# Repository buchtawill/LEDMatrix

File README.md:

# LEDMatrix
12x32 SMD LED matrix using ATmega328

### LED matrix 0805
This folder contains the schematic board files for the physical device.

### Image Stuff
Contains the java program that takes a jpg and generates an array that can be read by the ATmega.

### led-matrix
Contains the C++ code that runs on the ATmega. The Arduino development environment was used.

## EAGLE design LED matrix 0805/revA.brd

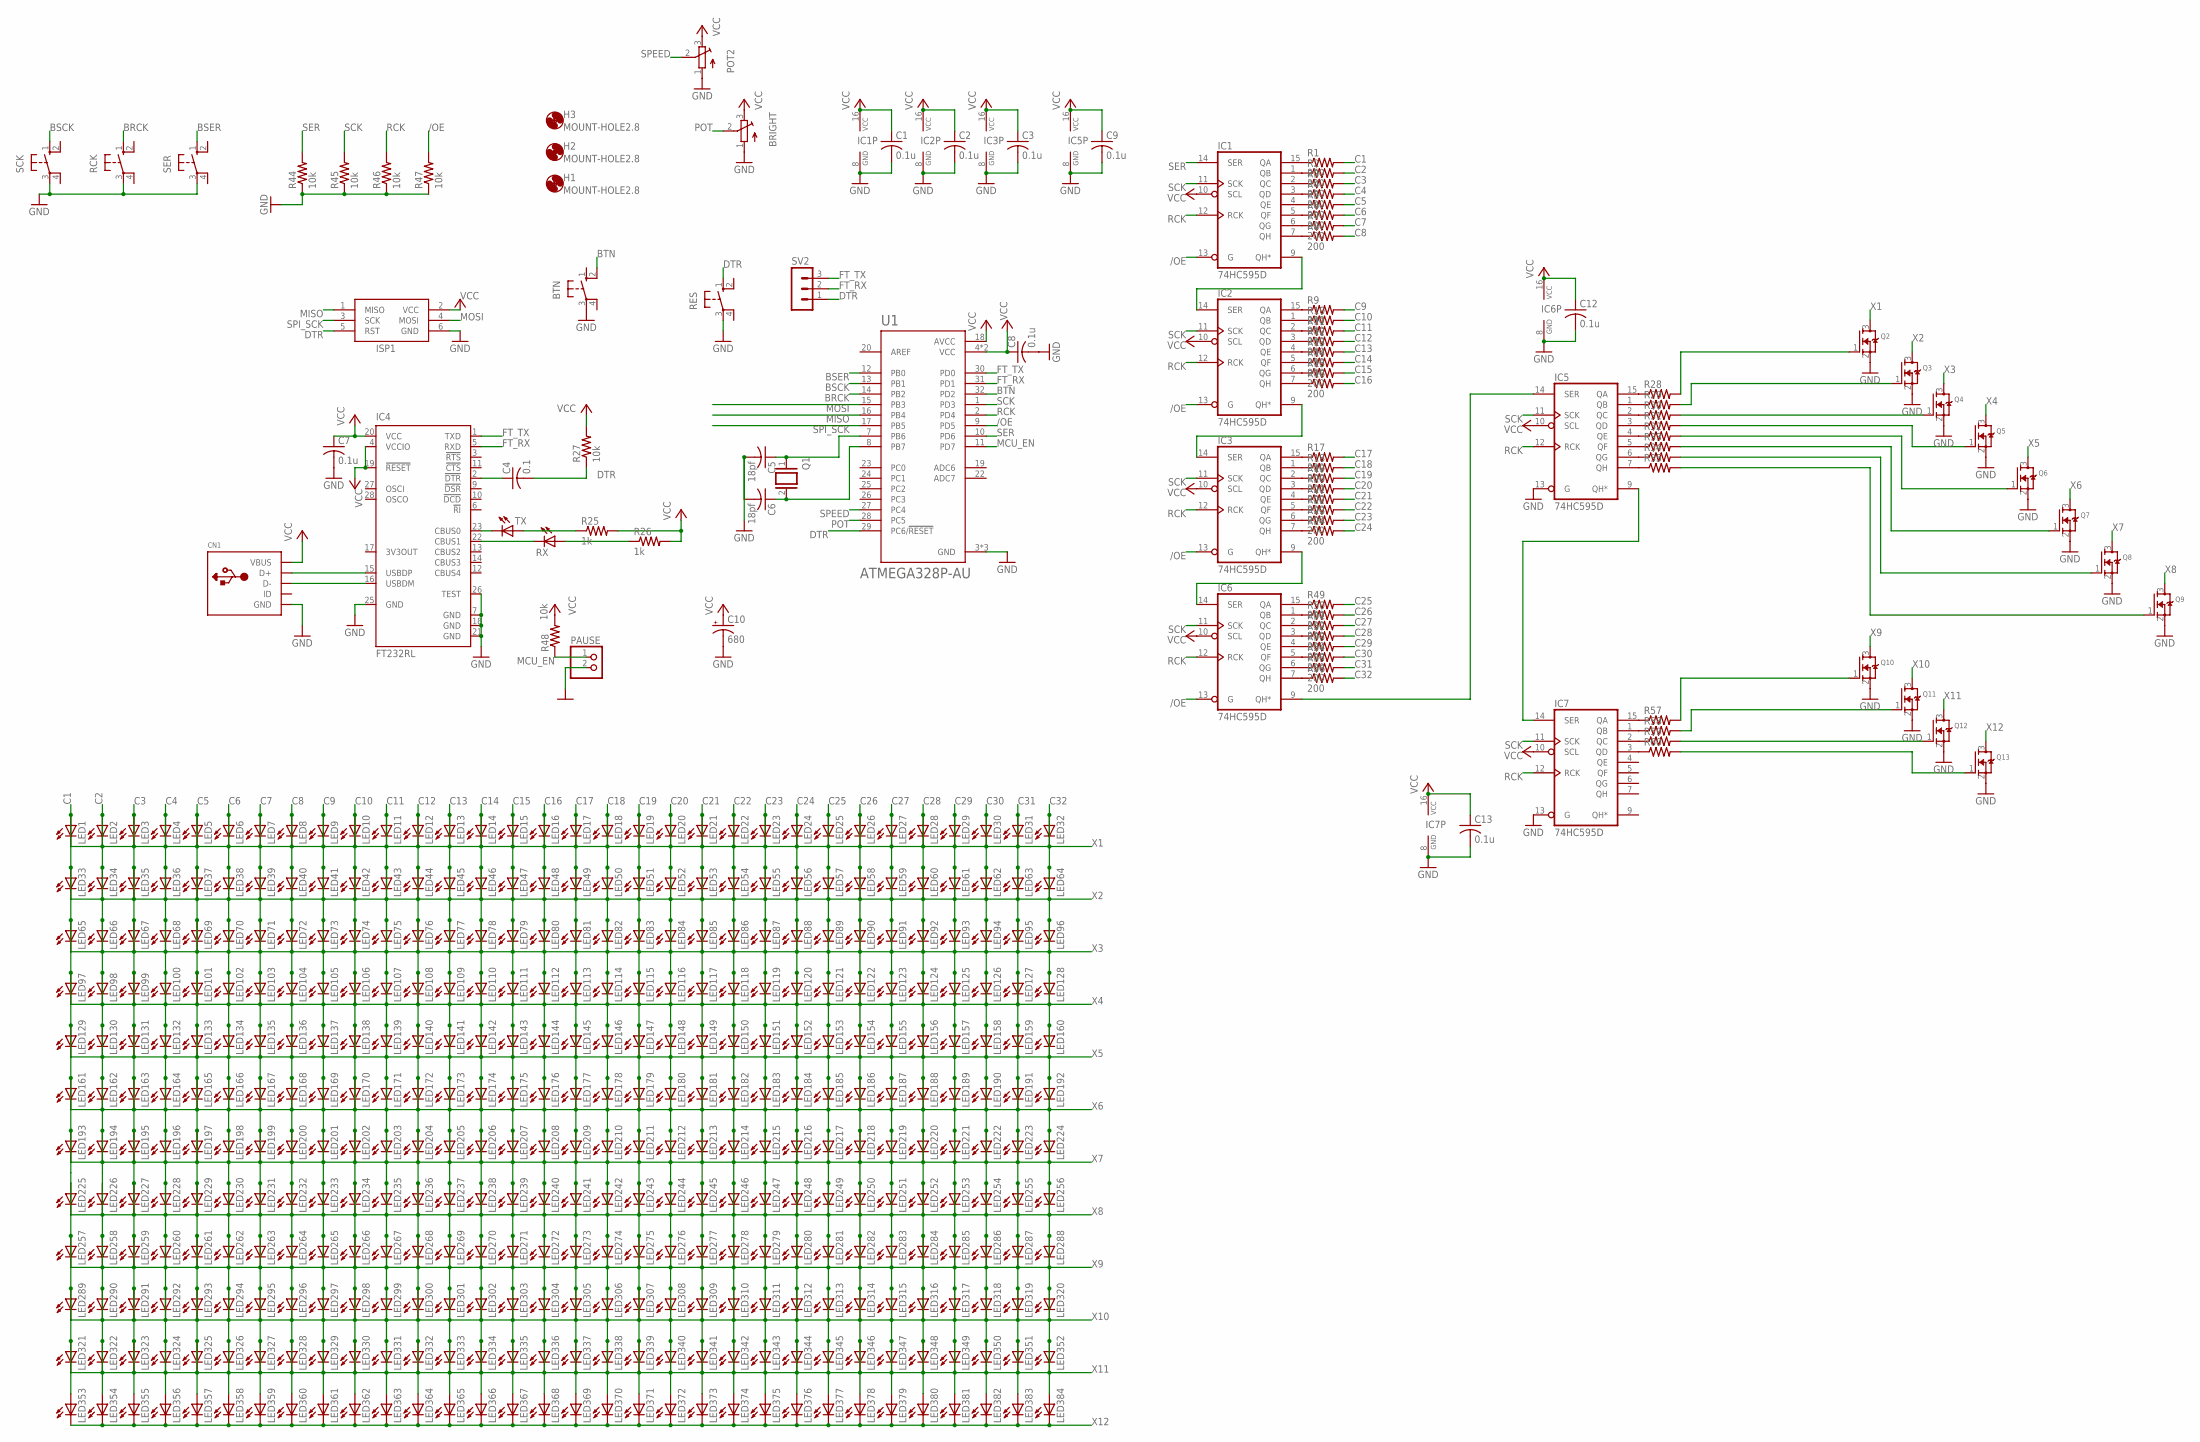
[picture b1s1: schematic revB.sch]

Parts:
BRIGHT: TRIMPOTTC33X; TC33X
BTN: 10-XX; B3F-10XX
C1, C2, C3, C7, C8, C9, C12, C13: 0.1u; C0805K
C4: 0.1; C0805K
C5, C6: 18pf; C0805K
C10: 680; E3,5-8
CN1: USBMINIB; USB-MINIB
H1, H2, H3: MOUNT-HOLE2.8; 2,8
IC1, IC2, IC3, IC5, IC6, IC7: 74HC595D; SO16
IC4: FT232RL; SSOP28
ISP1: AVRISP-6; AVRISP
LED1, LED2, LED3, LED4, LED5, LED6, LED7, LED8, LED9, LED10, LED11, LED12, LED13, LED14, LED15, LED16, LED17, LED18, LED19, LED20, LED21, LED22, LED23, LED24, LED25, LED26, LED27, LED28, LED29, LED30, LED31, LED32, LED33, LED34, LED35, LED36, LED37, LED38, LED39, LED40, LED41, LED42, LED43, LED44, LED45, LED46, LED47, LED48, LED49, LED50, LED51, LED52, LED53, LED54, LED55, LED56, LED57, LED58, LED59, LED60, LED61, LED62, LED63, LED64, LED65, LED66, LED67, LED68, LED69, LED70, LED71, LED72, LED73, LED74, LED75, LED76, LED77, LED78, LED79, LED80, LED81, LED82, LED83, LED84, LED85, LED86, LED87, LED88, LED89, LED90, LED91, LED92, LED93, LED94, LED95, LED96, LED97, LED98, LED99, LED100, LED101, LED102, LED103, LED104, LED105, LED106, LED107, LED108, LED109, LED110, LED111, LED112, LED113, LED114, LED115, LED116, LED117, LED118, LED119, LED120, LED121, LED122, LED123, LED124, LED125, LED126, LED127, LED128, LED129, LED130, LED131, LED132, LED133, LED134, LED135, LED136, LED137, LED138, LED139, LED140, LED141, LED142, LED143, LED144, LED145, LED146, LED147, LED148, LED149, LED150, LED151, LED152, LED153, LED154, LED155, LED156, LED157, LED158, LED159, LED160, LED161, LED162, LED163, LED164, LED165, LED166, LED167, LED168, LED169, LED170, LED171, LED172, LED173, LED174, LED175, LED176, LED177, LED178, LED179, LED180, LED181, LED182, LED183, LED184, LED185, LED186, LED187, LED188, LED189, LED190, LED191, LED192, LED193, LED194, LED195, LED196, LED197, LED198, LED199, LED200, LED201, LED202, LED203, LED204, LED205, LED206, LED207, LED208, LED209, LED210, LED211, LED212, LED213, LED214, LED215, LED216, LED217, LED218, LED219, LED220, LED221, LED222, LED223, LED224, LED225, LED226, LED227, LED228, LED229, LED230, LED231, LED232, LED233, LED234, LED235, LED236, LED237, LED238, LED239, LED240, LED241, LED242, LED243, LED244, LED245, LED246, LED247, LED248, LED249, LED250, LED251, LED252, LED253, LED254, LED255, LED256, LED257, LED258, LED259, LED260, LED261, LED262, LED263, LED264, LED265, LED266, LED267, LED268, LED269, LED270, LED271, LED272, LED273, LED274, LED275, LED276, LED277, LED278, LED279, LED280, LED281, LED282, LED283, LED284, LED285, LED286, LED287, LED288, LED289, LED290, LED291, LED292, LED293, LED294, LED295, LED296, LED297, LED298, LED299, LED300, LED301, LED302, LED303, LED304, LED305, LED306, LED307, LED308, LED309, LED310, LED311, LED312, LED313, LED314, LED315, LED316, LED317, LED318, LED319, LED320, LED321, LED322, LED323, LED324, LED325, LED326, LED327, LED328, LED329, LED330, LED331, LED332, LED333, LED334, LED335, LED336, LED337, LED338, LED339, LED340, LED341, LED342, LED343, LED344, LED345, LED346, LED347, LED348, LED349, LED350, LED351, LED352, LED353, LED354, LED355, LED356, LED357, LED358, LED359, LED360, LED361, LED362, LED363, LED364, LED365, LED366, LED367, LED368, LED369, LED370, LED371, LED372, LED373, LED374, LED375, LED376, LED377, LED378, LED379, LED380, LED381, LED382, LED383, LED384: LEDCHIP-LED0805; CHIP-LED0805
PAUSE: PINHD-1X2; 1X02
POT2: TRIMPOTTC33X; TC33X
Q1: XTAL/S; QS
Q2, Q3, Q4, Q5, Q6, Q7, Q8, Q9, Q10, Q11, Q12, Q13: MOSFET-NREFLOW; SOT23
R1, R2, R3, R4, R5, R6, R7, R8, R9, R10, R11, R12, R13, R14, R15, R16, R17, R18, R19, R20, R21, R22, R23, R24, R49, R50, R51, R52, R53, R54, R55, R56: 200; R0805
R25, R26: 1k; R0805
R27, R44, R45, R46, R47, R48: 10k; R0805
R28, R29, R30, R31, R32, R33, R34, R35, R57, R58, R59, R60: R-US_R0805; R0805
RCK: 10-XX; B3F-10XX
RES: 10-XX; B3F-10XX
RX: LEDCHIPLED_0805; CHIPLED_0805
SCK: 10-XX; B3F-10XX
SER: 10-XX; B3F-10XX
SV2: MA03-1
TX: LEDCHIPLED_0805; CHIPLED_0805
U1: ATMEGA328P-AU; QFP80P900X900X120-32N

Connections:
/OE: IC1.13 (G), IC2.13 (G), IC3.13 (G), IC6.13 (G), R47.2, U1.9 (PD5)
BRCK: RCK.1 (S), U1.14 (PB2)
BSCK: SCK.1 (S), U1.13 (PB1)
BSER: SER.1 (S), U1.12 (PB0)
BTN: BTN.2 (S1), U1.32 (PD2)
C1: LED1.A, LED33.A, LED65.A, LED97.A, LED129.A, LED161.A, LED193.A, LED225.A, LED257.A, LED289.A, LED321.A, LED353.A, R1.2
C2: LED2.A, LED34.A, LED66.A, LED98.A, LED130.A, LED162.A, LED194.A, LED226.A, LED258.A, LED290.A, LED322.A, LED354.A, R2.2
C3: LED3.A, LED35.A, LED67.A, LED99.A, LED131.A, LED163.A, LED195.A, LED227.A, LED259.A, LED291.A, LED323.A, LED355.A, R3.2
C4: LED4.A, LED36.A, LED68.A, LED100.A, LED132.A, LED164.A, LED196.A, LED228.A, LED260.A, LED292.A, LED324.A, LED356.A, R4.2
C5: LED5.A, LED37.A, LED69.A, LED101.A, LED133.A, LED165.A, LED197.A, LED229.A, LED261.A, LED293.A, LED325.A, LED357.A, R5.2
C6: LED6.A, LED38.A, LED70.A, LED102.A, LED134.A, LED166.A, LED198.A, LED230.A, LED262.A, LED294.A, LED326.A, LED358.A, R6.2
C7: LED7.A, LED39.A, LED71.A, LED103.A, LED135.A, LED167.A, LED199.A, LED231.A, LED263.A, LED295.A, LED327.A, LED359.A, R7.2
C8: LED8.A, LED40.A, LED72.A, LED104.A, LED136.A, LED168.A, LED200.A, LED232.A, LED264.A, LED296.A, LED328.A, LED360.A, R8.2
C9: LED9.A, LED41.A, LED73.A, LED105.A, LED137.A, LED169.A, LED201.A, LED233.A, LED265.A, LED297.A, LED329.A, LED361.A, R9.2
C10: LED10.A, LED42.A, LED74.A, LED106.A, LED138.A, LED170.A, LED202.A, LED234.A, LED266.A, LED298.A, LED330.A, LED362.A, R10.2
C11: LED11.A, LED43.A, LED75.A, LED107.A, LED139.A, LED171.A, LED203.A, LED235.A, LED267.A, LED299.A, LED331.A, LED363.A, R11.2
C12: LED12.A, LED44.A, LED76.A, LED108.A, LED140.A, LED172.A, LED204.A, LED236.A, LED268.A, LED300.A, LED332.A, LED364.A, R12.2
C13: LED13.A, LED45.A, LED77.A, LED109.A, LED141.A, LED173.A, LED205.A, LED237.A, LED269.A, LED301.A, LED333.A, LED365.A, R13.2
C14: LED14.A, LED46.A, LED78.A, LED110.A, LED142.A, LED174.A, LED206.A, LED238.A, LED270.A, LED302.A, LED334.A, LED366.A, R14.2
C15: LED15.A, LED47.A, LED79.A, LED111.A, LED143.A, LED175.A, LED207.A, LED239.A, LED271.A, LED303.A, LED335.A, LED367.A, R15.2
C16: LED16.A, LED48.A, LED80.A, LED112.A, LED144.A, LED176.A, LED208.A, LED240.A, LED272.A, LED304.A, LED336.A, LED368.A, R16.2
C17: LED17.A, LED49.A, LED81.A, LED113.A, LED145.A, LED177.A, LED209.A, LED241.A, LED273.A, LED305.A, LED337.A, LED369.A, R17.2
C18: LED18.A, LED50.A, LED82.A, LED114.A, LED146.A, LED178.A, LED210.A, LED242.A, LED274.A, LED306.A, LED338.A, LED370.A, R18.2
C19: LED19.A, LED51.A, LED83.A, LED115.A, LED147.A, LED179.A, LED211.A, LED243.A, LED275.A, LED307.A, LED339.A, LED371.A, R19.2
C20: LED20.A, LED52.A, LED84.A, LED116.A, LED148.A, LED180.A, LED212.A, LED244.A, LED276.A, LED308.A, LED340.A, LED372.A, R20.2
C21: LED21.A, LED53.A, LED85.A, LED117.A, LED149.A, LED181.A, LED213.A, LED245.A, LED277.A, LED309.A, LED341.A, LED373.A, R21.2
C22: LED22.A, LED54.A, LED86.A, LED118.A, LED150.A, LED182.A, LED214.A, LED246.A, LED278.A, LED310.A, LED342.A, LED374.A, R22.2
C23: LED23.A, LED55.A, LED87.A, LED119.A, LED151.A, LED183.A, LED215.A, LED247.A, LED279.A, LED311.A, LED343.A, LED375.A, R23.2
C24: LED24.A, LED56.A, LED88.A, LED120.A, LED152.A, LED184.A, LED216.A, LED248.A, LED280.A, LED312.A, LED344.A, LED376.A, R24.2
C25: LED25.A, LED57.A, LED89.A, LED121.A, LED153.A, LED185.A, LED217.A, LED249.A, LED281.A, LED313.A, LED345.A, LED377.A, R49.2
C26: LED26.A, LED58.A, LED90.A, LED122.A, LED154.A, LED186.A, LED218.A, LED250.A, LED282.A, LED314.A, LED346.A, LED378.A, R50.2
C27: LED27.A, LED59.A, LED91.A, LED123.A, LED155.A, LED187.A, LED219.A, LED251.A, LED283.A, LED315.A, LED347.A, LED379.A, R51.2
C28: LED28.A, LED60.A, LED92.A, LED124.A, LED156.A, LED188.A, LED220.A, LED252.A, LED284.A, LED316.A, LED348.A, LED380.A, R52.2
C29: LED29.A, LED61.A, LED93.A, LED125.A, LED157.A, LED189.A, LED221.A, LED253.A, LED285.A, LED317.A, LED349.A, LED381.A, R53.2
C30: LED30.A, LED62.A, LED94.A, LED126.A, LED158.A, LED190.A, LED222.A, LED254.A, LED286.A, LED318.A, LED350.A, LED382.A, R54.2
C31: LED31.A, LED63.A, LED95.A, LED127.A, LED159.A, LED191.A, LED223.A, LED255.A, LED287.A, LED319.A, LED351.A, LED383.A, R55.2
C32: LED32.A, LED64.A, LED96.A, LED128.A, LED160.A, LED192.A, LED224.A, LED256.A, LED288.A, LED320.A, LED352.A, LED384.A, R56.2
DTR: C4.2, ISP1.5 (RST), R27.1, RES.1 (S), SV2.1, U1.29 (PC6/!RESET)
FT_RX: IC4.5 (RXD), SV2.2, U1.31 (PD1)
FT_TX: IC4.1 (TXD), SV2.3, U1.30 (PD0)
GND: BRIGHT.1 (A), BTN.3, C1.2, C2.2, C3.2, C5.2, C6.2, C7.2, C8.2, C9.2, C10.-, C12.2, C13.2, CN1.GND, IC1.8 (GND), IC2.8 (GND), IC3.8 (GND), IC4.7 (GND), IC4.18 (GND), IC4.21 (GND), IC4.25 (GND), IC4.26 (TEST), IC5.8 (GND), IC5.13 (G), IC6.8 (GND), IC7.8 (GND), IC7.13 (G), ISP1.6 (GND), PAUSE.2, POT2.1 (A), Q2.2 (S), Q3.2 (S), Q4.2 (S), Q5.2 (S), Q6.2 (S), Q7.2 (S), Q8.2 (S), Q9.2 (S), Q10.2 (S), Q11.2 (S), Q12.2 (S), Q13.2 (S), R44.1, R45.1, R46.1, R47.1, RCK.3, RES.3, SCK.3, SER.3, U1.3 (GND), U1.5 (GND), U1.21 (GND)
MCU_EN: PAUSE.1, R48.1, U1.11 (PD7)
MISO: ISP1.1 (MISO), U1.16 (PB4)
MOSI: ISP1.4 (MOSI), U1.15 (PB3)
unnamed: IC1.9 (QH*), IC2.14 (SER)
unnamed: IC1.15 (QA), R1.1
unnamed: IC1.1 (QB), R2.1
unnamed: IC1.2 (QC), R3.1
unnamed: IC1.3 (QD), R4.1
unnamed: IC1.4 (QE), R5.1
unnamed: IC1.5 (QF), R6.1
unnamed: IC1.6 (QG), R7.1
unnamed: IC1.7 (QH), R8.1
unnamed: IC2.15 (QA), R9.1
unnamed: IC2.1 (QB), R10.1
unnamed: IC2.2 (QC), R11.1
unnamed: IC2.3 (QD), R12.1
unnamed: IC2.4 (QE), R13.1
unnamed: IC2.5 (QF), R14.1
unnamed: IC2.6 (QG), R15.1
unnamed: IC2.7 (QH), R16.1
unnamed: IC2.9 (QH*), IC3.14 (SER)
unnamed: IC3.15 (QA), R17.1
unnamed: IC3.1 (QB), R18.1
unnamed: IC3.2 (QC), R19.1
unnamed: IC3.3 (QD), R20.1
unnamed: IC3.4 (QE), R21.1
unnamed: IC3.5 (QF), R22.1
unnamed: IC3.6 (QG), R23.1
unnamed: IC3.7 (QH), R24.1
unnamed: CN1.D+, IC4.15 (USBDP)
unnamed: CN1.D-, IC4.16 (USBDM)
unnamed: IC4.23 (CBUS0), TX.C
unnamed: IC4.22 (CBUS1), RX.C
unnamed: R25.1, TX.A
unnamed: R26.1, RX.A
unnamed: C6.1, Q1.2, U1.8 (PB7)
unnamed: C5.1, Q1.1, U1.7 (PB6)
unnamed: IC3.9 (QH*), IC6.14 (SER)
unnamed: IC6.15 (QA), R49.1
unnamed: IC5.15 (QA), R28.1
unnamed: IC5.1 (QB), R29.1
unnamed: IC5.2 (QC), R30.1
unnamed: IC5.3 (QD), R31.1
unnamed: IC5.4 (QE), R32.1
unnamed: IC5.5 (QF), R33.1
unnamed: IC5.6 (QG), R34.1
unnamed: IC5.7 (QH), R35.1
unnamed: Q2.1 (G), R28.2
unnamed: Q3.1 (G), R29.2
unnamed: Q4.1 (G), R30.2
unnamed: Q5.1 (G), R31.2
unnamed: Q6.1 (G), R32.2
unnamed: Q7.1 (G), R33.2
unnamed: Q8.1 (G), R34.2
unnamed: Q9.1 (G), R35.2
unnamed: IC6.1 (QB), R50.1
unnamed: IC6.2 (QC), R51.1
unnamed: IC6.3 (QD), R52.1
unnamed: IC6.4 (QE), R53.1
unnamed: IC6.5 (QF), R54.1
unnamed: IC6.6 (QG), R55.1
unnamed: IC6.7 (QH), R56.1
unnamed: IC5.14 (SER), IC6.9 (QH*)
unnamed: IC7.15 (QA), R57.1
unnamed: IC7.1 (QB), R58.1
unnamed: IC7.2 (QC), R59.1
unnamed: IC7.3 (QD), R60.1
unnamed: C4.1, IC4.2 (!DTR)
unnamed: Q10.1 (G), R57.2
unnamed: Q11.1 (G), R58.2
unnamed: Q12.1 (G), R59.2
unnamed: Q13.1 (G), R60.2
unnamed: IC5.9 (QH*), IC7.14 (SER)
POT: BRIGHT.2 (S), U1.28 (PC5)
RCK: IC1.12 (RCK), IC2.12 (RCK), IC3.12 (RCK), IC5.12 (RCK), IC6.12 (RCK), IC7.12 (RCK), R46.2, U1.2 (PD4)
SCK: IC1.11 (SCK), IC2.11 (SCK), IC3.11 (SCK), IC5.11 (SCK), IC6.11 (SCK), IC7.11 (SCK), R45.2, U1.1 (PD3)
SER: IC1.14 (SER), R44.2, U1.10 (PD6)
SPEED: POT2.2 (S), U1.27 (PC4)
SPI_SCK: ISP1.3 (SCK), U1.17 (PB5)
VCC: BRIGHT.3 (E), C1.1, C2.1, C3.1, C7.1, C8.1, C9.1, C10.+, C12.1, C13.1, CN1.VBUS, IC1.10 (SCL), IC1.16 (VCC), IC2.10 (SCL), IC2.16 (VCC), IC3.10 (SCL), IC3.16 (VCC), IC4.4 (VCCIO), IC4.19 (!RESET), IC4.20 (VCC), IC5.10 (SCL), IC5.16 (VCC), IC6.10 (SCL), IC6.16 (VCC), IC7.10 (SCL), IC7.16 (VCC), ISP1.2 (VCC), POT2.3 (E), R25.2, R26.2, R27.2, R48.2, U1.4 (VCC), U1.6 (VCC), U1.18 (AVCC)
X1: LED1.C, LED2.C, LED3.C, LED4.C, LED5.C, LED6.C, LED7.C, LED8.C, LED9.C, LED10.C, LED11.C, LED12.C, LED13.C, LED14.C, LED15.C, LED16.C, LED17.C, LED18.C, LED19.C, LED20.C, LED21.C, LED22.C, LED23.C, LED24.C, LED25.C, LED26.C, LED27.C, LED28.C, LED29.C, LED30.C, LED31.C, LED32.C, Q2.3 (D)
X2: LED33.C, LED34.C, LED35.C, LED36.C, LED37.C, LED38.C, LED39.C, LED40.C, LED41.C, LED42.C, LED43.C, LED44.C, LED45.C, LED46.C, LED47.C, LED48.C, LED49.C, LED50.C, LED51.C, LED52.C, LED53.C, LED54.C, LED55.C, LED56.C, LED57.C, LED58.C, LED59.C, LED60.C, LED61.C, LED62.C, LED63.C, LED64.C, Q3.3 (D)
X3: LED65.C, LED66.C, LED67.C, LED68.C, LED69.C, LED70.C, LED71.C, LED72.C, LED73.C, LED74.C, LED75.C, LED76.C, LED77.C, LED78.C, LED79.C, LED80.C, LED81.C, LED82.C, LED83.C, LED84.C, LED85.C, LED86.C, LED87.C, LED88.C, LED89.C, LED90.C, LED91.C, LED92.C, LED93.C, LED94.C, LED95.C, LED96.C, Q4.3 (D)
X4: LED97.C, LED98.C, LED99.C, LED100.C, LED101.C, LED102.C, LED103.C, LED104.C, LED105.C, LED106.C, LED107.C, LED108.C, LED109.C, LED110.C, LED111.C, LED112.C, LED113.C, LED114.C, LED115.C, LED116.C, LED117.C, LED118.C, LED119.C, LED120.C, LED121.C, LED122.C, LED123.C, LED124.C, LED125.C, LED126.C, LED127.C, LED128.C, Q5.3 (D)
X5: LED129.C, LED130.C, LED131.C, LED132.C, LED133.C, LED134.C, LED135.C, LED136.C, LED137.C, LED138.C, LED139.C, LED140.C, LED141.C, LED142.C, LED143.C, LED144.C, LED145.C, LED146.C, LED147.C, LED148.C, LED149.C, LED150.C, LED151.C, LED152.C, LED153.C, LED154.C, LED155.C, LED156.C, LED157.C, LED158.C, LED159.C, LED160.C, Q6.3 (D)
X6: LED161.C, LED162.C, LED163.C, LED164.C, LED165.C, LED166.C, LED167.C, LED168.C, LED169.C, LED170.C, LED171.C, LED172.C, LED173.C, LED174.C, LED175.C, LED176.C, LED177.C, LED178.C, LED179.C, LED180.C, LED181.C, LED182.C, LED183.C, LED184.C, LED185.C, LED186.C, LED187.C, LED188.C, LED189.C, LED190.C, LED191.C, LED192.C, Q7.3 (D)
X7: LED193.C, LED194.C, LED195.C, LED196.C, LED197.C, LED198.C, LED199.C, LED200.C, LED201.C, LED202.C, LED203.C, LED204.C, LED205.C, LED206.C, LED207.C, LED208.C, LED209.C, LED210.C, LED211.C, LED212.C, LED213.C, LED214.C, LED215.C, LED216.C, LED217.C, LED218.C, LED219.C, LED220.C, LED221.C, LED222.C, LED223.C, LED224.C, Q8.3 (D)
X8: LED225.C, LED226.C, LED227.C, LED228.C, LED229.C, LED230.C, LED231.C, LED232.C, LED233.C, LED234.C, LED235.C, LED236.C, LED237.C, LED238.C, LED239.C, LED240.C, LED241.C, LED242.C, LED243.C, LED244.C, LED245.C, LED246.C, LED247.C, LED248.C, LED249.C, LED250.C, LED251.C, LED252.C, LED253.C, LED254.C, LED255.C, LED256.C, Q9.3 (D)
X9: LED257.C, LED258.C, LED259.C, LED260.C, LED261.C, LED262.C, LED263.C, LED264.C, LED265.C, LED266.C, LED267.C, LED268.C, LED269.C, LED270.C, LED271.C, LED272.C, LED273.C, LED274.C, LED275.C, LED276.C, LED277.C, LED278.C, LED279.C, LED280.C, LED281.C, LED282.C, LED283.C, LED284.C, LED285.C, LED286.C, LED287.C, LED288.C, Q10.3 (D)
X10: LED289.C, LED290.C, LED291.C, LED292.C, LED293.C, LED294.C, LED295.C, LED296.C, LED297.C, LED298.C, LED299.C, LED300.C, LED301.C, LED302.C, LED303.C, LED304.C, LED305.C, LED306.C, LED307.C, LED308.C, LED309.C, LED310.C, LED311.C, LED312.C, LED313.C, LED314.C, LED315.C, LED316.C, LED317.C, LED318.C, LED319.C, LED320.C, Q11.3 (D)
X11: LED321.C, LED322.C, LED323.C, LED324.C, LED325.C, LED326.C, LED327.C, LED328.C, LED329.C, LED330.C, LED331.C, LED332.C, LED333.C, LED334.C, LED335.C, LED336.C, LED337.C, LED338.C, LED339.C, LED340.C, LED341.C, LED342.C, LED343.C, LED344.C, LED345.C, LED346.C, LED347.C, LED348.C, LED349.C, LED350.C, LED351.C, LED352.C, Q12.3 (D)
X12: LED353.C, LED354.C, LED355.C, LED356.C, LED357.C, LED358.C, LED359.C, LED360.C, LED361.C, LED362.C, LED363.C, LED364.C, LED365.C, LED366.C, LED367.C, LED368.C, LED369.C, LED370.C, LED371.C, LED372.C, LED373.C, LED374.C, LED375.C, LED376.C, LED377.C, LED378.C, LED379.C, LED380.C, LED381.C, LED382.C, LED383.C, LED384.C, Q13.3 (D)

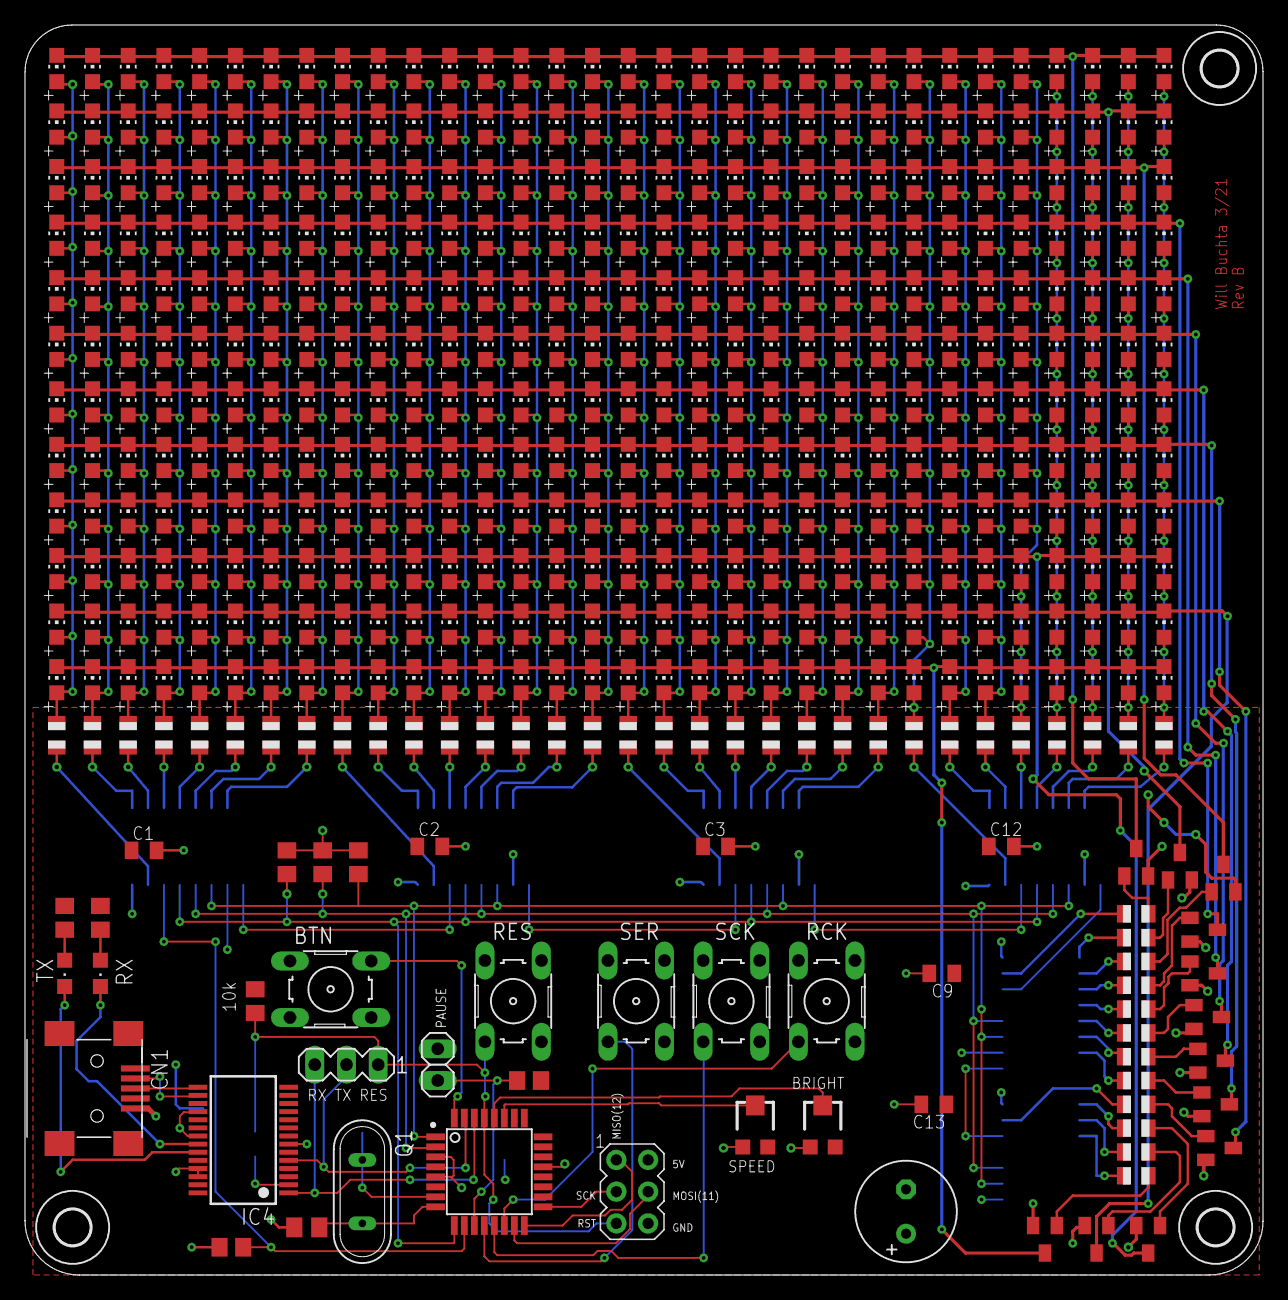
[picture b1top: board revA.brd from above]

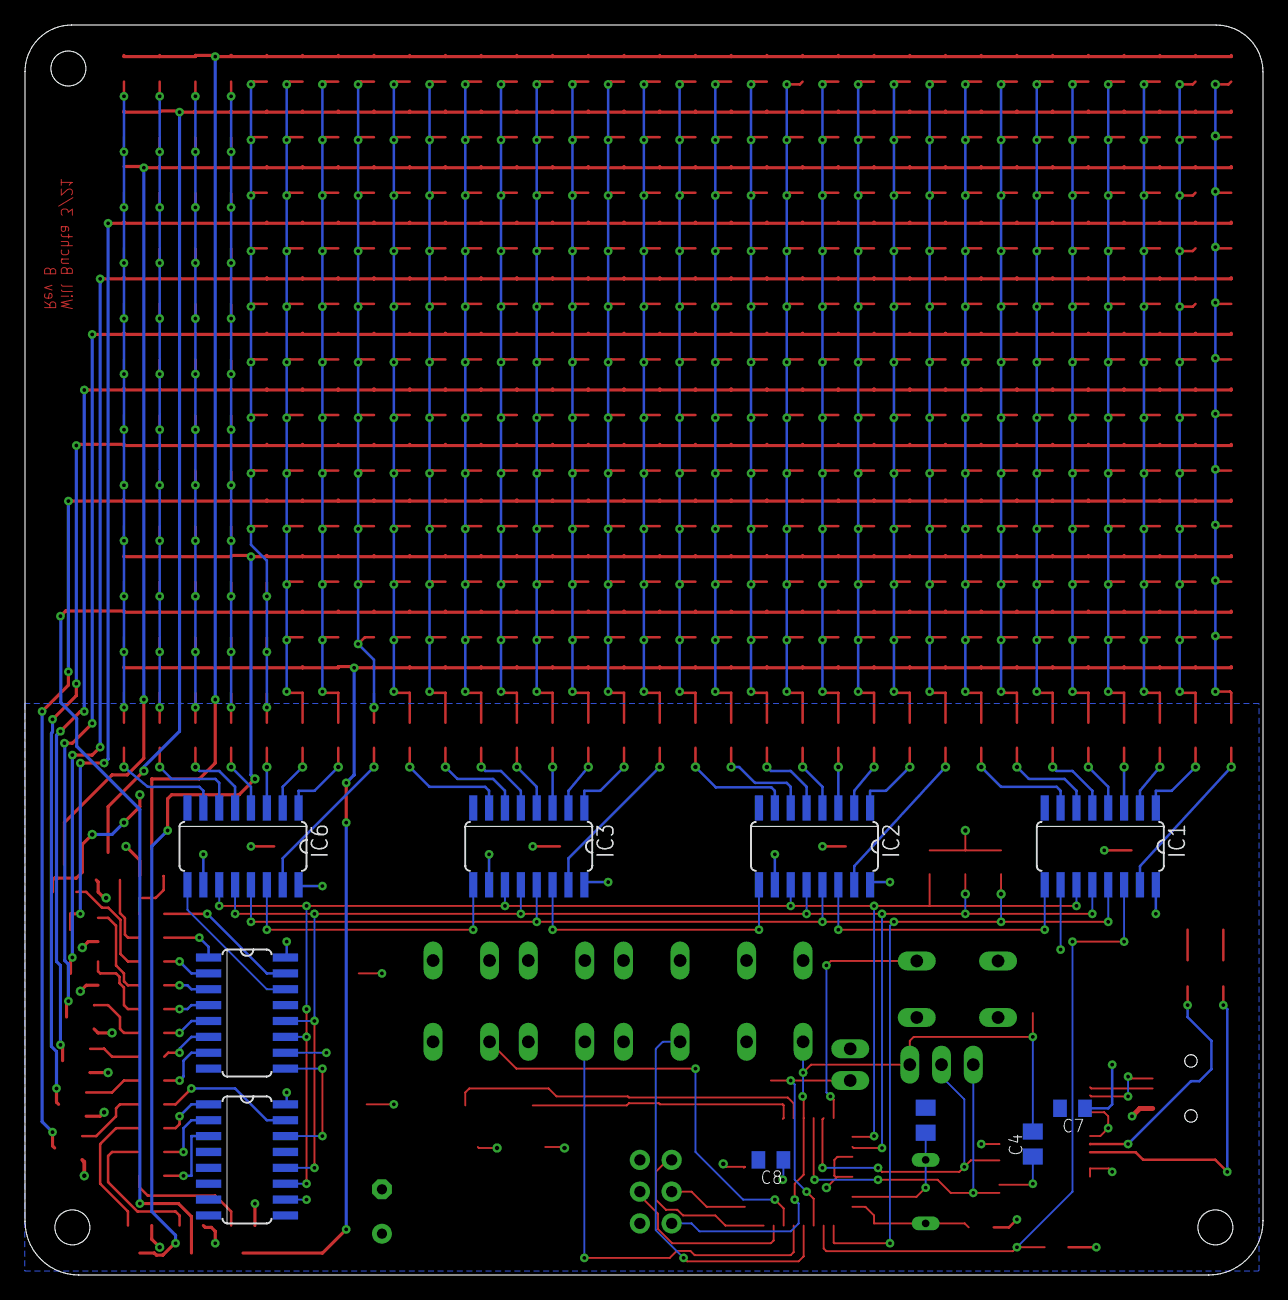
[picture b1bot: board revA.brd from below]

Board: 2 copper layers, 99.0 x 100.0 mm, 485 parts (10 on the bottom side), 133 nets.

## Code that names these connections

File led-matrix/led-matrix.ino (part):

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#include <avr/wdt.h>

#define BUTTON 2
#define SER 6 //port d 6
#define SCK 3
#define RCK 4
#define OE  5
#define HALT 7

#define BSER 8
#define BSCK 9
#define BRCK 10

#define UP 69   //for shifting
#define DOWN 15
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  potVal = map(potVal, 0, 1023, 1, upperTimer);
  setTimer(potVal, upperTimer);
  PORTD &= ~(1 << OE); //disable output, turn on LEDs
  pinMode(BSER, INPUT_PULLUP);
  pinMode(BSCK, INPUT_PULLUP);
  pinMode(BRCK, INPUT_PULLUP);
  pinMode(BUTTON, INPUT_PULLUP);
  attachInterrupt(digitalPinToInterrupt(BUTTON), buttonMethod, FALLING);
  //for (int i = 0; i < 500; i++)render();
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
